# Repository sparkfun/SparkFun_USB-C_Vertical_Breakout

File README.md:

SparkFun USB-C Vertical Mount Breakout
======================================

[*SparkFun USB-C Breakout - Vertical (BOB-23055)*](https://www.sparkfun.com/products/23055)

With this USB-C breakout you will be able to incorporate a vertical USB-C connector into your projects without needing to solder each tiny SMD pad. The vertical orientation of the USB-C connector is also convenient for panel mounts in projects.

The SparkFun USB-C Breakout supplies up to three times the power as our previous USB breakouts *(i.e. Type-A, micro-B, and mini-B)* and also solves the universally frustrating dilemma of plugging a USB cable in correctly because it's reversible! The board breaks out the USB-C connector's `VBUS`, `GND`, `CC1`, `CC2`, `D+`, `D-`, and `SHLD` pins into a 0.1" pitch header while providing up to a nominal 1.5A of power and up to 3A depending on the upstream device.

Repository Contents
-------------------

* **/Hardware** - Eagle design files (.brd, .sch)
*   **/Production** - Production panel files (.brd)

Product Variants
----------------

* [BOB-23055](https://www.sparkfun.com/products/23055) - Vertical USB-C connector
* [BOB-15100](https://www.sparkfun.com/products/15100) - USB-C Breakout *(Horizontal USB-C connector)*

Version History
---------------

* [v10](https://github.com/sparkfun/SparkFun_USB-C_Vertical_Breakout/releases/tag/v01) - Initial Release

License Information
-------------------

This product is ***open source***!

Please review the [`LICENSE.md`](./LICENSE.md) file for license information.

If you have any questions or concerns about licensing, please contact technical support on our [SparkFun forums](https://forum.sparkfun.com/viewforum.php?f=152).

Distributed as-is; no warranty is given.

- Your friends at SparkFun.

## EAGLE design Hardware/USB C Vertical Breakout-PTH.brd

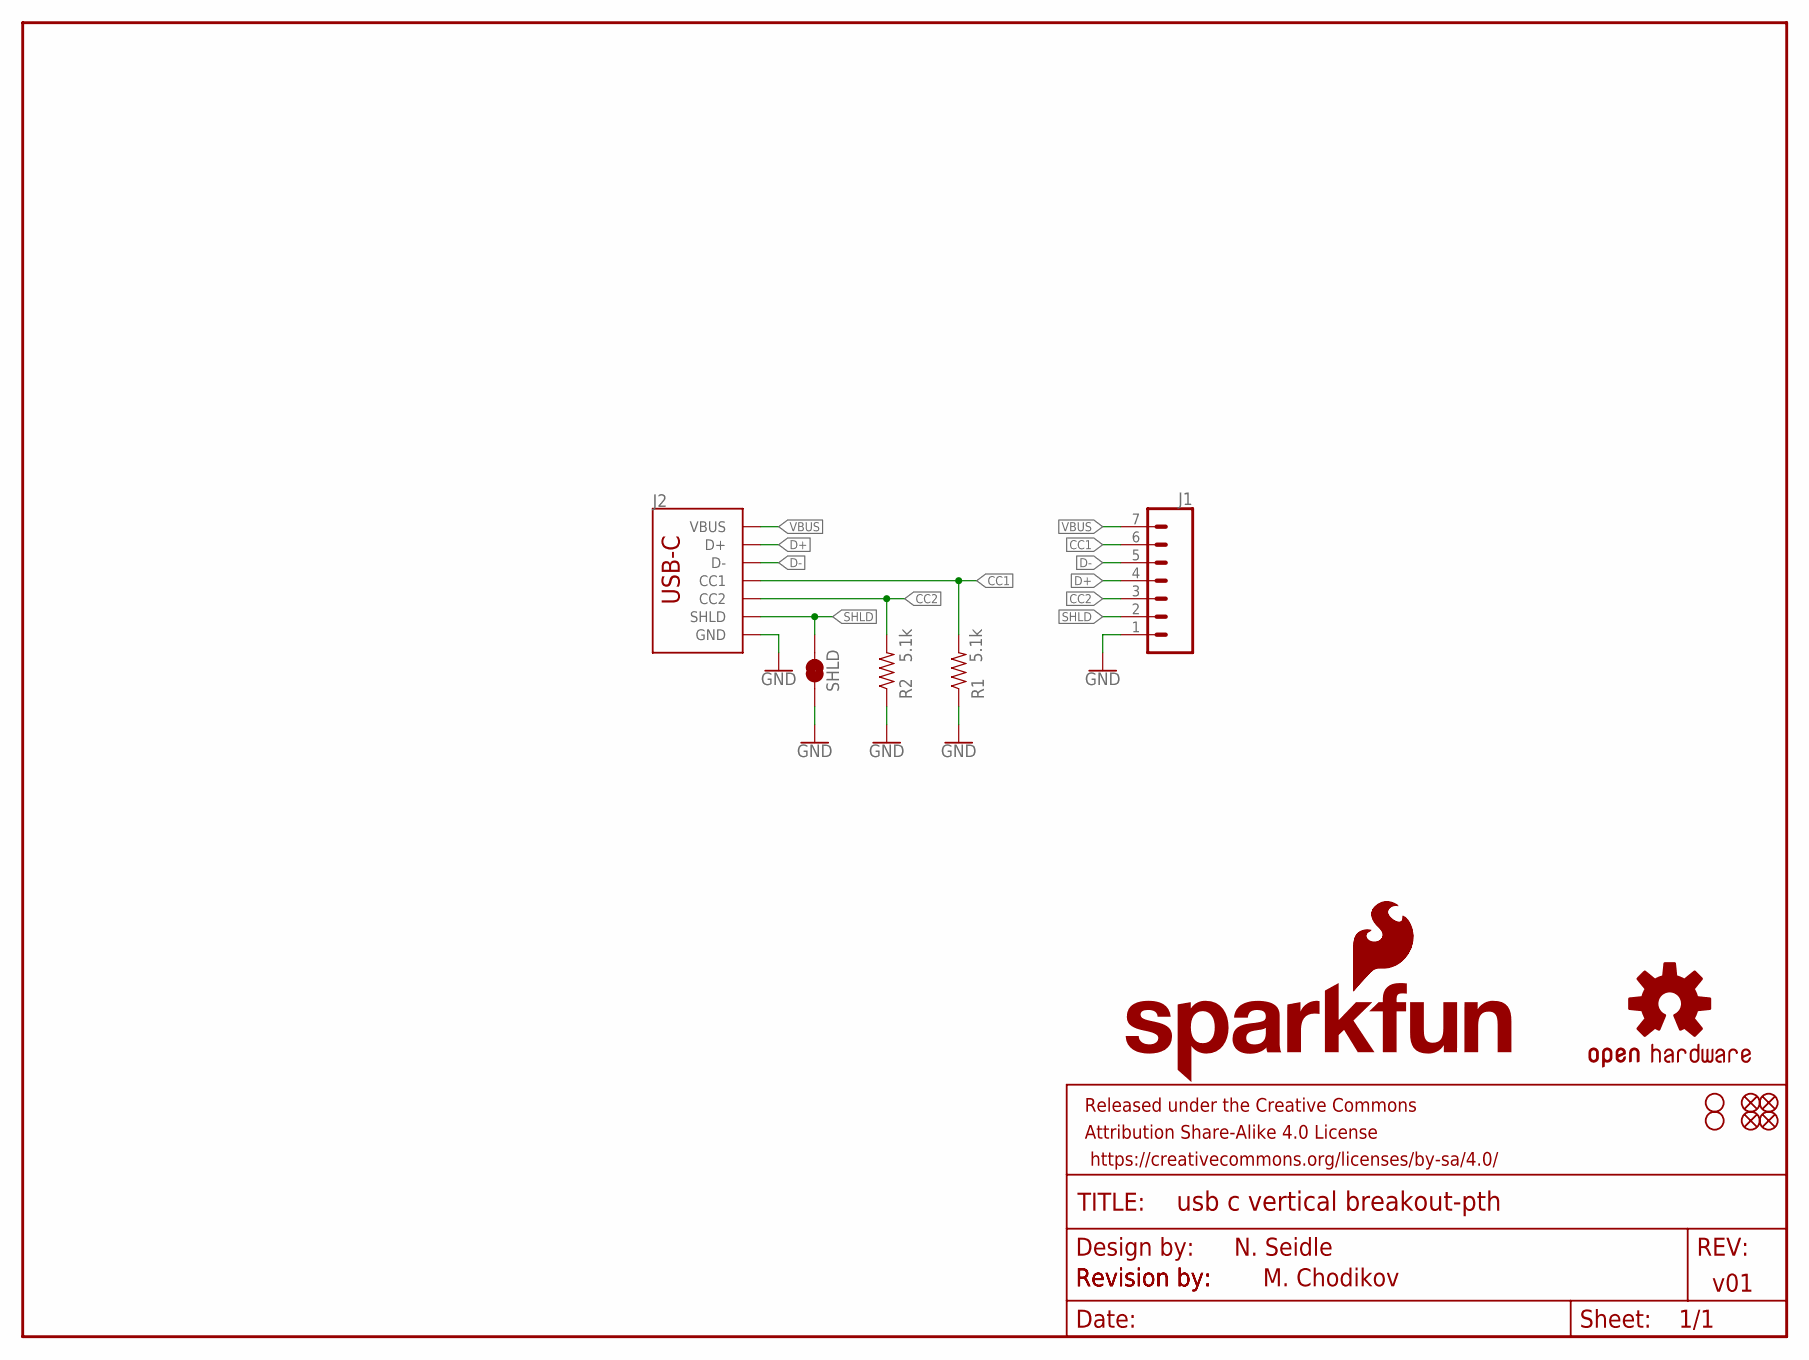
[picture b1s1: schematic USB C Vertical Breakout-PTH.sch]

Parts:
FD1, FD2, FD3, FD4: FIDUCIALUFIDUCIAL; FIDUCIAL-MICRO
FRAME2: FRAME-LETTER; CREATIVE_COMMONS
H1, H2: STAND-OFFTIGHT; STAND-OFF-TIGHT
J1: CONN_07NO_SILK; 1X07_NO_SILK
J2: USB_C_2-LAYER-VERTICAL-PTH; USB-C-8P-2LAYER-VERTICAL-PTH
LOGO1: SFE_LOGO_NAME_FLAMEBLANK; BLANK
LOGO2: OSHW-LOGOMINI; OSHW-LOGO-MINI
LOGO3: SFE_LOGO_FLAME.1_INCH; SFE_LOGO_FLAME_.1
R1, R2: 5.1k; 0603
SHLD: SHLD; SMT-JUMPER_2_NC_TRACE_NO-SILK

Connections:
CC1: J1.6, J2.A5 (CC1), R1.2
CC2: J1.3, J2.B5 (CC2), R2.2
D+: J1.4, J2.A6 (D+), J2.B6 (D+)
D-: J1.5, J2.A7 (D-), J2.B7 (D-)
GND: J1.1, J2.A1 (GND), J2.A12 (GND), J2.B1 (GND), J2.B12 (GND), R1.1, R2.1, SHLD.1
SHLD: J1.2, J2.SHLD1 (SHLD), J2.SHLD2 (SHLD), J2.SHLD3 (SHLD), J2.SHLD4 (SHLD), SHLD.2
VBUS: J1.7, J2.A4 (VBUS), J2.A9 (VBUS), J2.B4 (VBUS), J2.B9 (VBUS)

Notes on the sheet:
v01
N. Seidle
Revision by:
M. Chodikov

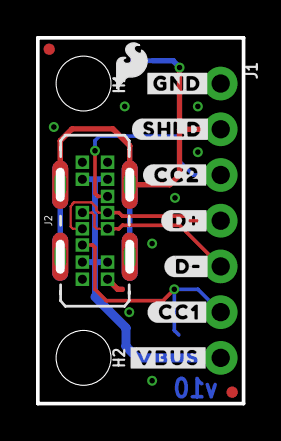
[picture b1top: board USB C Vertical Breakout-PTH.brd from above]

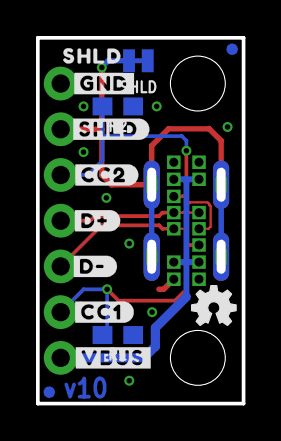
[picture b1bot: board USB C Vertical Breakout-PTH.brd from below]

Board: 2 copper layers, 11.4 x 20.3 mm, 31 parts (14 on the bottom side), 7 nets.

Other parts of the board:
U$1: SHLD0
U$4: #D##3
U$7: #D##4
U$10, U$21: #GND#6
U$16: #CC2#0
U$17: #CC1#5
U$18: #SHLD#5
U$19, U$20: #VBUS#7
U$22: #SHLD#8
U$23: #CC2#9
U$24: #D##9
U$25: #D##10
U$26: #CC1#11
U$59: ORDERING_INSTRUCTIONS

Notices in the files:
parts and their libraries:
SparkFun-Aesthetics: Licensing: Creative Commons ShareAlike 4.0 International - https://creativecommons.org/licenses/by-sa/4.0
SparkFun-Aesthetics: Released under the Creative Commons Attribution Share-Alike 4.0 License
SparkFun-Aesthetics: https://creativecommons.org/licenses/by-sa/4.0
